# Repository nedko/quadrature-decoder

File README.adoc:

[NOTE]
This is Work In Progress

Quadrature decoder for use with a rotary (A&B wires type) encoder.

Features:

 * Clock-less operation. That is, no clocks, even within the chips.
   This is a good for audio prosumer and hi-fi uses,
   or any other uses where noise emission is to be kept low,
   e.g. Frequency knob of HAM radio VFO.
 * Analog output (at least 12bit - 4096 steps) *slow* analog DAC,
   via covox-style resistor network.
 * Relatively cheap to build.

As stated in the top note, the project is Work In Progress.
That is, there is no physically built prototype yet.

The clock-less operation also means asynchronous operation of the
logic. That is, a finite state automatas are have their state
transitioned at clock ticks that are part of the input. In this case,
the clock input is the rotary encoder itself. When rotary encoder does
not move, no logic switches will occur. The aimed design is with DIP
packaged CMOS logic chips from CD40XX series, as they are (currently
and fortunately) relatively cheap and easy to assemble in small volumes
by human with some soldering skills. PCBs of a SMD design variant of
the same schematics are usually populated by specialized machines, but
with some skill the PCB can be populated manually by humans too.

Tools:

 * KiCAD - schematics and PCB design

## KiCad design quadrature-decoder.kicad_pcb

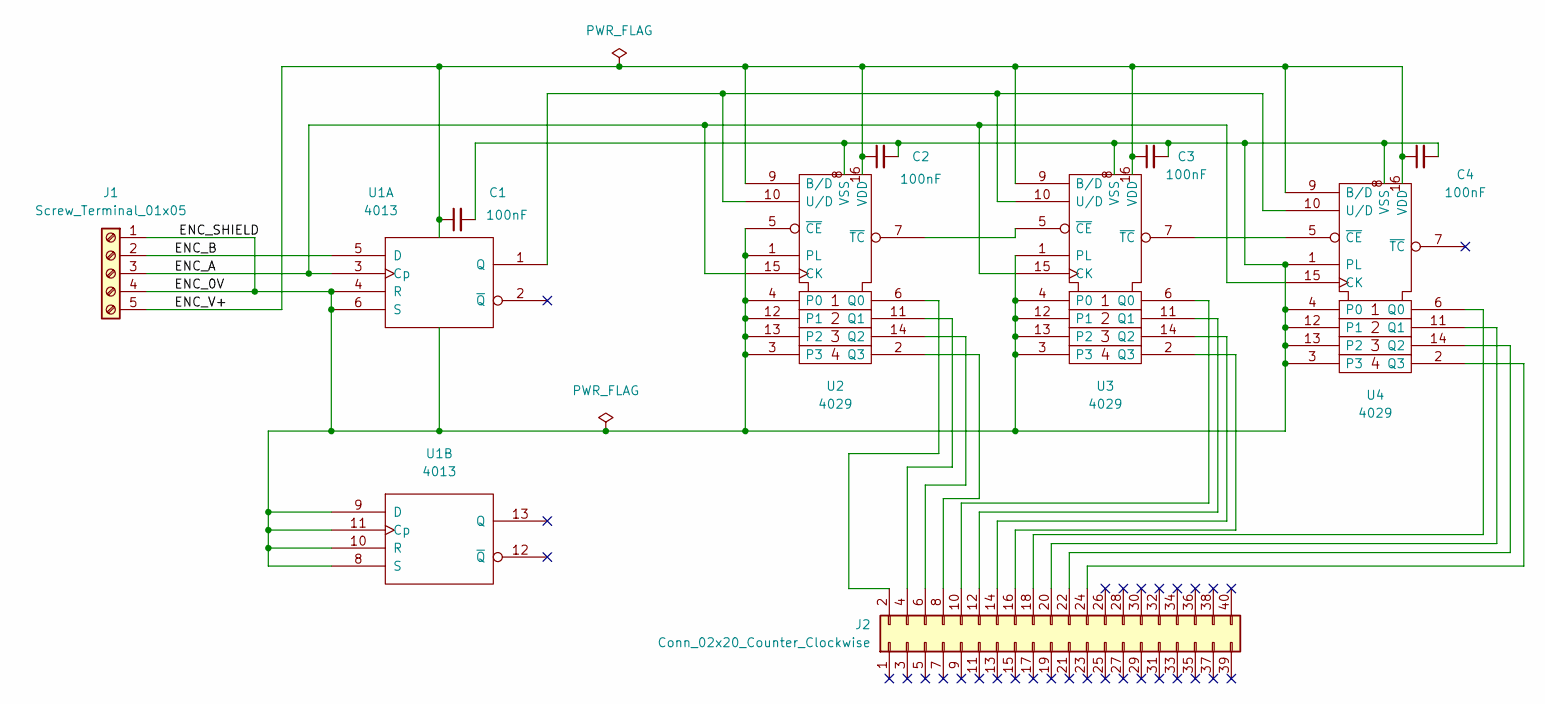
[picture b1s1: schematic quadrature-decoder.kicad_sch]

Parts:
C1, C2, C3, C4: 100nF; C_Axial_L3.8mm_D2.6mm_P7.50mm_Horizontal
J1: Screw_Terminal_01x05; TerminalBlock_bornier-5_P5.08mm
J2: Conn_02x20_Counter_Clockwise; IDC-Header_2x20_P2.54mm_Vertical
U1: 4013; DIP-14_W7.62mm_Socket_LongPads
U2, U3, U4: 4029; DIP-16_W7.62mm_Socket_LongPads

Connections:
/ENC_A: J1.3, U1.3 (Cp), U2.15 (CK), U3.15 (CK), U4.15 (CK)
/ENC_B: J1.2, U1.5 (D)
unnamed: J2.2, U2.6 (Q0)
unnamed: J2.4, U2.11 (Q1)
unnamed: J2.6, U2.14 (Q2)
unnamed: J2.8, U2.2 (Q3)
unnamed: J2.10, U3.6 (Q0)
unnamed: J2.12, U3.11 (Q1)
unnamed: J2.14, U3.14 (Q2)
unnamed: J2.16, U3.2 (Q3)
unnamed: J2.18, U4.6 (Q0)
unnamed: J2.20, U4.11 (Q1)
unnamed: J2.22, U4.14 (Q2)
unnamed: J2.24, U4.2 (Q3)
unnamed: U1.1 (Q), U2.10 (U/D), U3.10 (U/D), U4.10 (U/D)
unnamed: U2.7 (~TC), U3.5 (~CE)
unnamed: U3.7 (~TC), U4.5 (~CE)
Vdd: C1.1, C2.1, C3.1, C4.1, J1.5, U1.14 (Vdd), U2.9 (B/D), U2.16 (VDD), U3.9 (B/D), U3.16 (VDD), U4.9 (B/D), U4.16 (VDD)
Vss: C1.2, C2.2, C3.2, C4.2, J1.1, J1.4, U1.4 (R), U1.6 (S), U1.7 (Vss), U1.8 (S), U1.9 (D), U1.10 (R), U1.11 (Cp), U2.1 (PL), U2.3, U2.4 (P0), U2.5 (~CE), U2.8 (VSS), U2.12 (P1), U2.13 (P2), U3.1 (PL), U3.3, U3.4 (P0), U3.8 (VSS), U3.12 (P1), U3.13 (P2), U4.1 (PL), U4.3, U4.4 (P0), U4.8 (VSS), U4.12 (P1), U4.13 (P2)

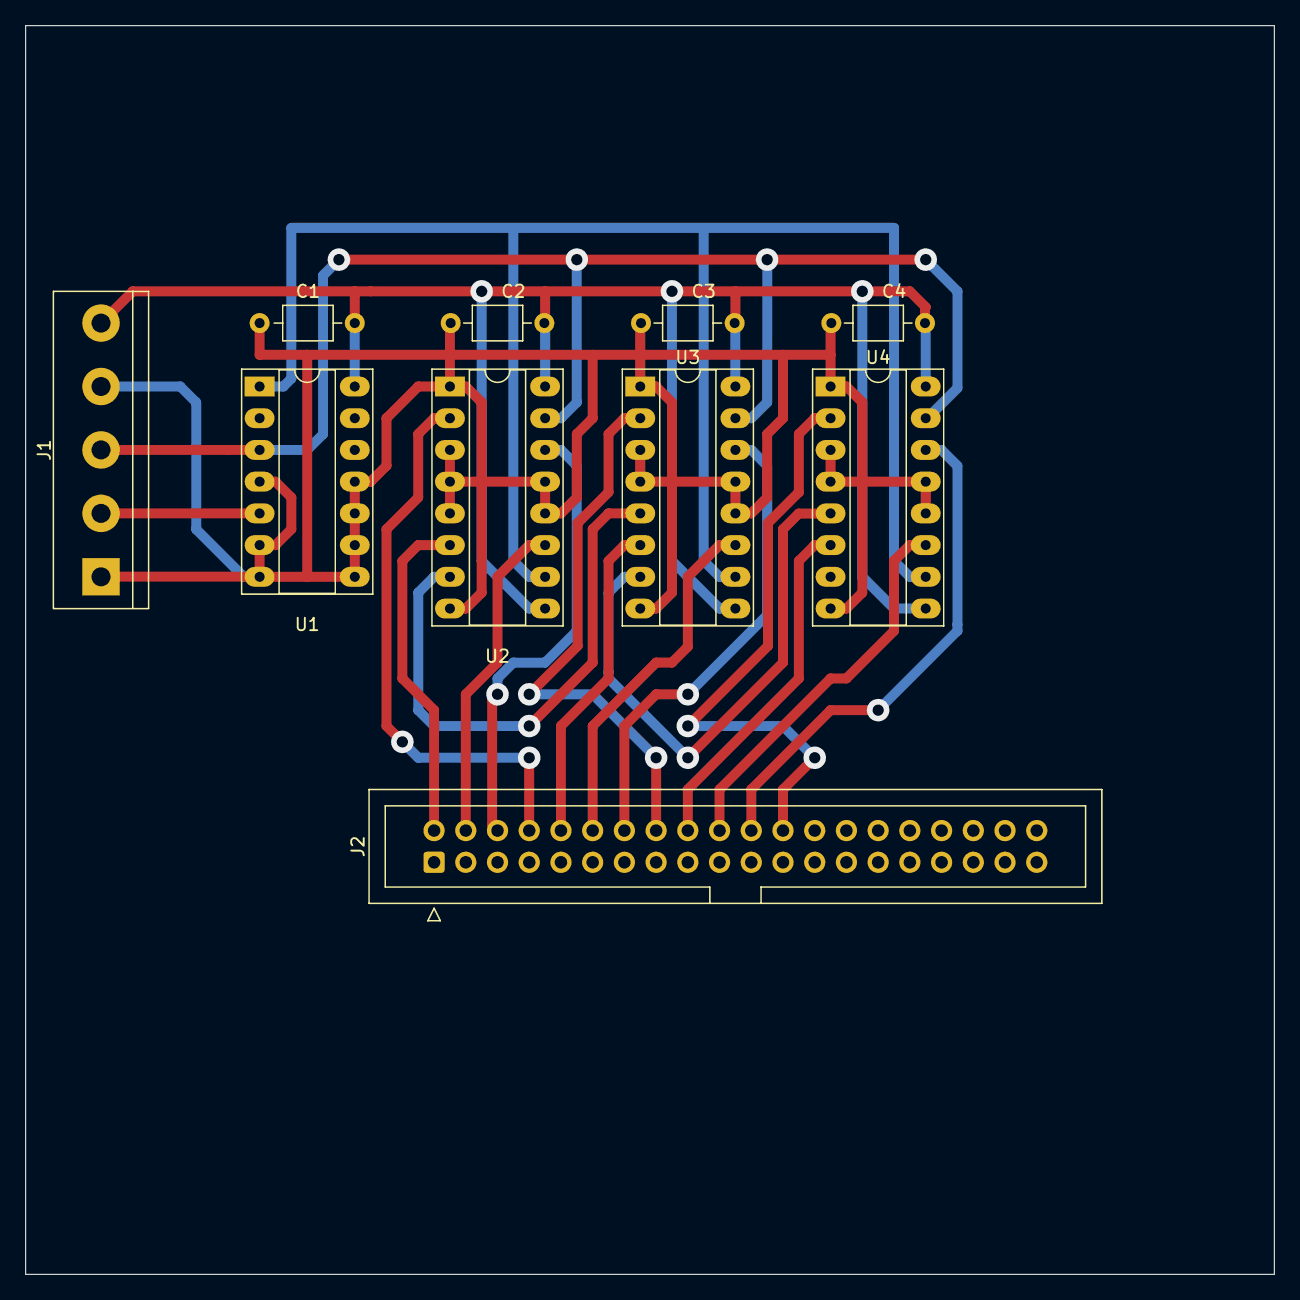
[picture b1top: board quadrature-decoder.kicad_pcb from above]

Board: 2 copper layers, 100.0 x 100.0 mm, 10 parts (0 on the bottom side), 19 nets.

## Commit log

2022-11-10 Initial version of quadrature decoder in dedicated repository
2022-11-10 quadrature.kicad_* -> quadrature-decoder.kicad_*
2022-11-17 Improve routing and component positioning; add capacitors
2022-11-17 Add PCB view PNG images
2022-11-18 Fix typos in README.adoc
2023-02-11 add "Синтезатор частоты трансивера; Денисов В. (RA6LM), Ушич В. (UW6LI), Спирин В. (UA6LGY).html"
2023-02-12 Initial attempt on radio/90/1,2,3 synth as kicad project
2023-02-12 A2 module almost done; A2.pdf plot rendering
2023-02-12 Fix typo in A2 sheet title by changing it
